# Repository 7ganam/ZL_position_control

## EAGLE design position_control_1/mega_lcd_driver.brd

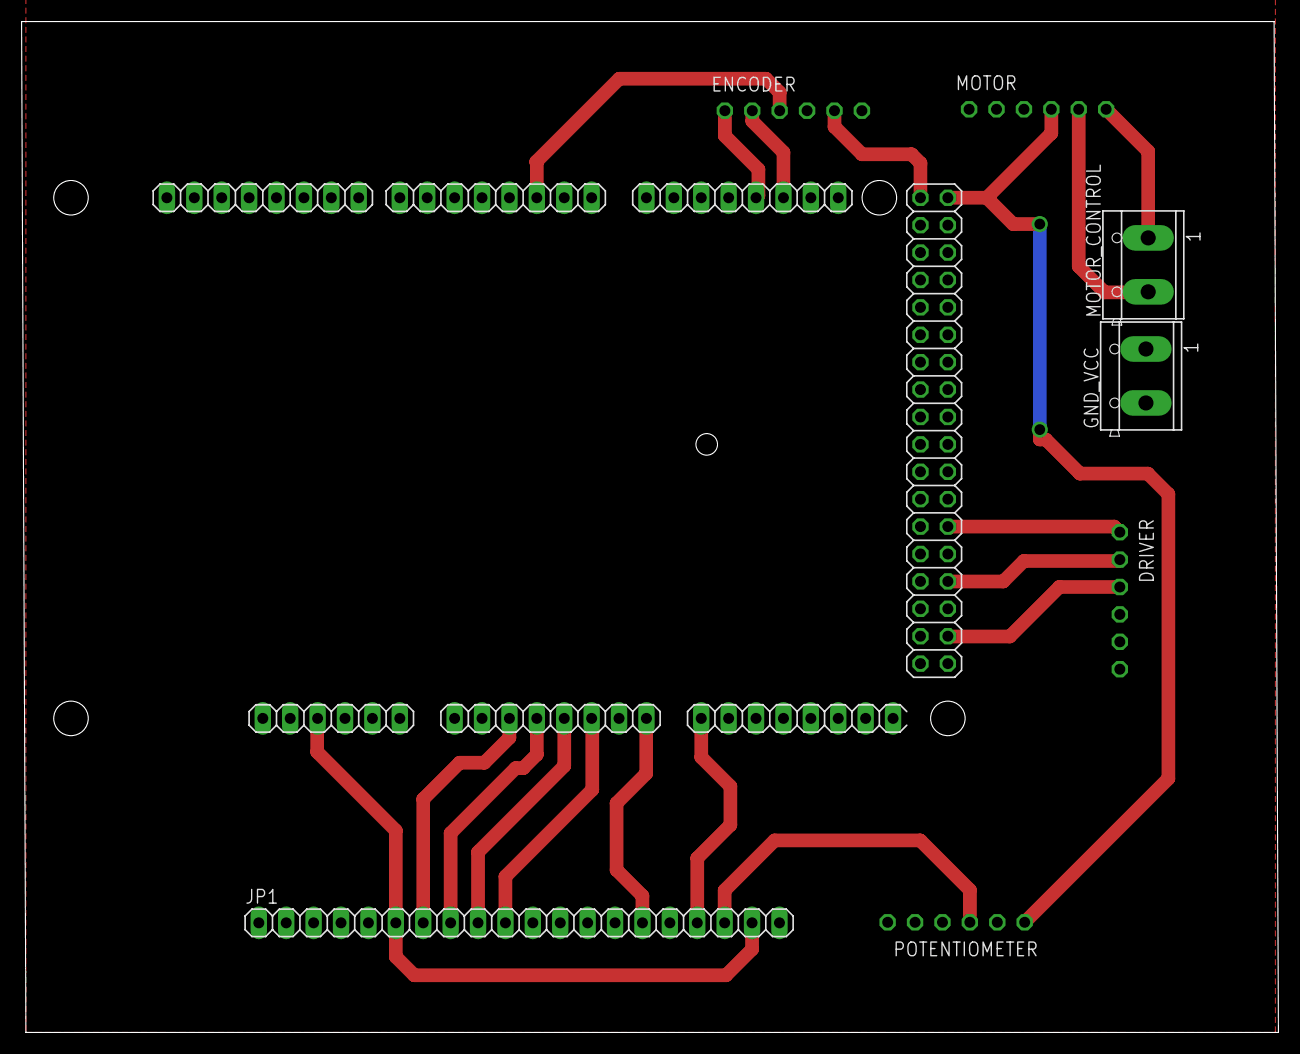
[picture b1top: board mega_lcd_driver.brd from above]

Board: 2 copper layers, 116.5 x 93.7 mm, 8 parts (0 on the bottom side), 17 nets.

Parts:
DRIVER: 1X06-CLEAN
ENCODER: 1X06-CLEAN
GND_VCC: CON_TERMINAL_BLOCK_02-5MM; TERMINAL_BLOCK_2P_5
IC1: MEGA_ARDUINO
JP1: 1X20
MOTOR: 1X06-CLEAN
MOTOR_CONTROL: CON_TERMINAL_BLOCK_02-5MM; TERMINAL_BLOCK_2P_5
POTENTIOMETER: 1X06-CLEAN

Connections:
+5V: ENCODER.5, IC1.3, IC1.47, IC1.48, JP1.6, JP1.19, MOTOR.4, POTENTIOMETER.1
GND: ENCODER.4, GND_VCC.1, IC1.4, IC1.5, IC1.45, IC1.81, IC1.82, JP1.5, JP1.16, JP1.20, MOTOR.3, POTENTIOMETER.5
unnamed: ENCODER.1, IC1.26
unnamed: ENCODER.2, IC1.25
unnamed: MOTOR.5, MOTOR_CONTROL.2
unnamed: MOTOR.6, MOTOR_CONTROL.1
unnamed: DRIVER.3, IC1.80
unnamed: DRIVER.2, IC1.76
unnamed: DRIVER.1, IC1.72
unnamed: JP1.18, POTENTIOMETER.3
unnamed: IC1.15, JP1.17
unnamed: IC1.11, JP1.9
unnamed: ENCODER.3, IC1.33
unnamed: IC1.14, JP1.15
unnamed: IC1.9, JP1.7
unnamed: IC1.12, JP1.10
unnamed: IC1.10, JP1.8

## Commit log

2020-04-23 all old files staged -- the repo needs to be re ordered later
2020-04-23 deleted unused files .. kept copy2 file as the main source codes
